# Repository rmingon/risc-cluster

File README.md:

# RISC-V Cluster Project

A distributed computing cluster based on CH32V RISC-V microcontrollers with Ethernet connectivity.

[HACKADAY](https://hackaday.io/project/204036-13ghz-for-only-10-bucks)

[TINDIE](https://www.tindie.com/products/rmingon/risc-v-cluster-13ghz-combined/)

## Overview

This project implements a cluster computing system using multiple CH32V microcontrollers connected via Ethernet. The system features a master controller (CH32V307RCT6) that coordinates with multiple worker nodes (CH32V003F4P6) to form a distributed computing network.

## Project pictures

## Hardware Design

### Master Controller

- **MCU**: CH32V307RCT6 (64-pin LQFP)
- **Features**:
  - RISC-V core with Ethernet MAC
  - USB connectivity for debugging and programming
  - Ethernet port (RJ45) for network communication
  - Power regulation (3.3V via AMS1117)

### Worker Nodes

- **MCU**: CH32V003F4P6 (24 units)
- **Features**:
  - Compact RISC-V microcontrollers
  - Individual LED indicators
  - Test points for debugging
  - Distributed across the PCB

### Key Components

- **Ethernet**: RJ45 connector with integrated magnetics
- **USB**: Micro-B connector for programming and debug
- **Power**: 3.3V regulation from USB input
- **Debug**: CH340C USB-to-UART bridge
- **Connectors**: Programming headers for JTAG/SWD access

## Project Structure

```
risc-cluster/
├── hardware/                 # KiCad PCB design files
│   ├── hardware.kicad_*     # Main PCB design files
│   ├── production/          # Manufacturing files
│   │   ├── bom.csv         # Bill of Materials
│   │   ├── positions.csv   # Pick and place data
│   │   └── hardware.zip    # Gerber files
│   └── hardware-backups/   # Design history backups
└── master/                  # Master controller firmware
    ├── Core/               # RISC-V core files
    ├── Debug/              # Debug utilities
    ├── Peripheral/         # CH32V30x peripheral drivers
    ├── Startup/            # Boot code
    └── User/               # Application code
```

## Bill of Materials

| Component    | Quantity | Description                        |
| ------------ | -------- | ---------------------------------- |
| CH32V307RCT6 | 1        | Master RISC-V MCU (LQFP-64)        |
| CH32V003F4P6 | 24       | Worker RISC-V MCUs (SOP-20)        |
| AMS1117-3.3  | 1        | 3.3V voltage regulator             |
| CH340C       | 1        | USB-to-UART bridge                 |
| LEDs         | 25       | Status indicators                  |
| Resistors    | 29       | Current limiting (0603)            |
| Capacitors   | 52       | Decoupling and filtering (0603)    |
| Connectors   | 5        | USB, Ethernet, programming headers |

## Development Setup

### Hardware Tools

- KiCad 7.0+ for PCB design
- Standard PCB fabrication (4-layer board)
- Pick and place assembly for SMD components

### Software Tools

- MounRiver Studio IDE (for CH32V development)
- WCH-LinkE programmer/debugger
- CH32V peripheral library

## Getting Started

1. **Hardware Assembly**: Use the production files in `hardware/production/` for PCB fabrication
2. **Master Firmware**: Build and flash the master controller code in `master/`
3. **Worker Firmware**: Develop and deploy worker node firmware for distributed tasks
4. **Network Setup**: Configure Ethernet connectivity for cluster communication

## Recent Development

Based on git history, recent work includes:

- Initial PCB layout with CH32V microcontrollers
- Ethernet connectivity implementation
- CH32V307 master controller integration
- MounRiver Studio project setup
- Production file generation

## License

This project is licensed under the CERN Open Hardware Licence Version 2 - Strongly Reciprocal (CERN-OHL-S v2).

The hardware design files are released under CERN-OHL-S v2, which ensures that any modifications or improvements to the hardware design must be shared under the same license terms.

Note: This project uses WCH (Nanjing Qinheng Microelectronics) peripheral libraries for firmware development, which are subject to their own licensing terms.

## Contributing

This is a hardware-software co-design project. Contributions welcome for:

- Firmware optimization
- Hardware design improvements
- Cluster algorithms implementation
- Documentation and examples

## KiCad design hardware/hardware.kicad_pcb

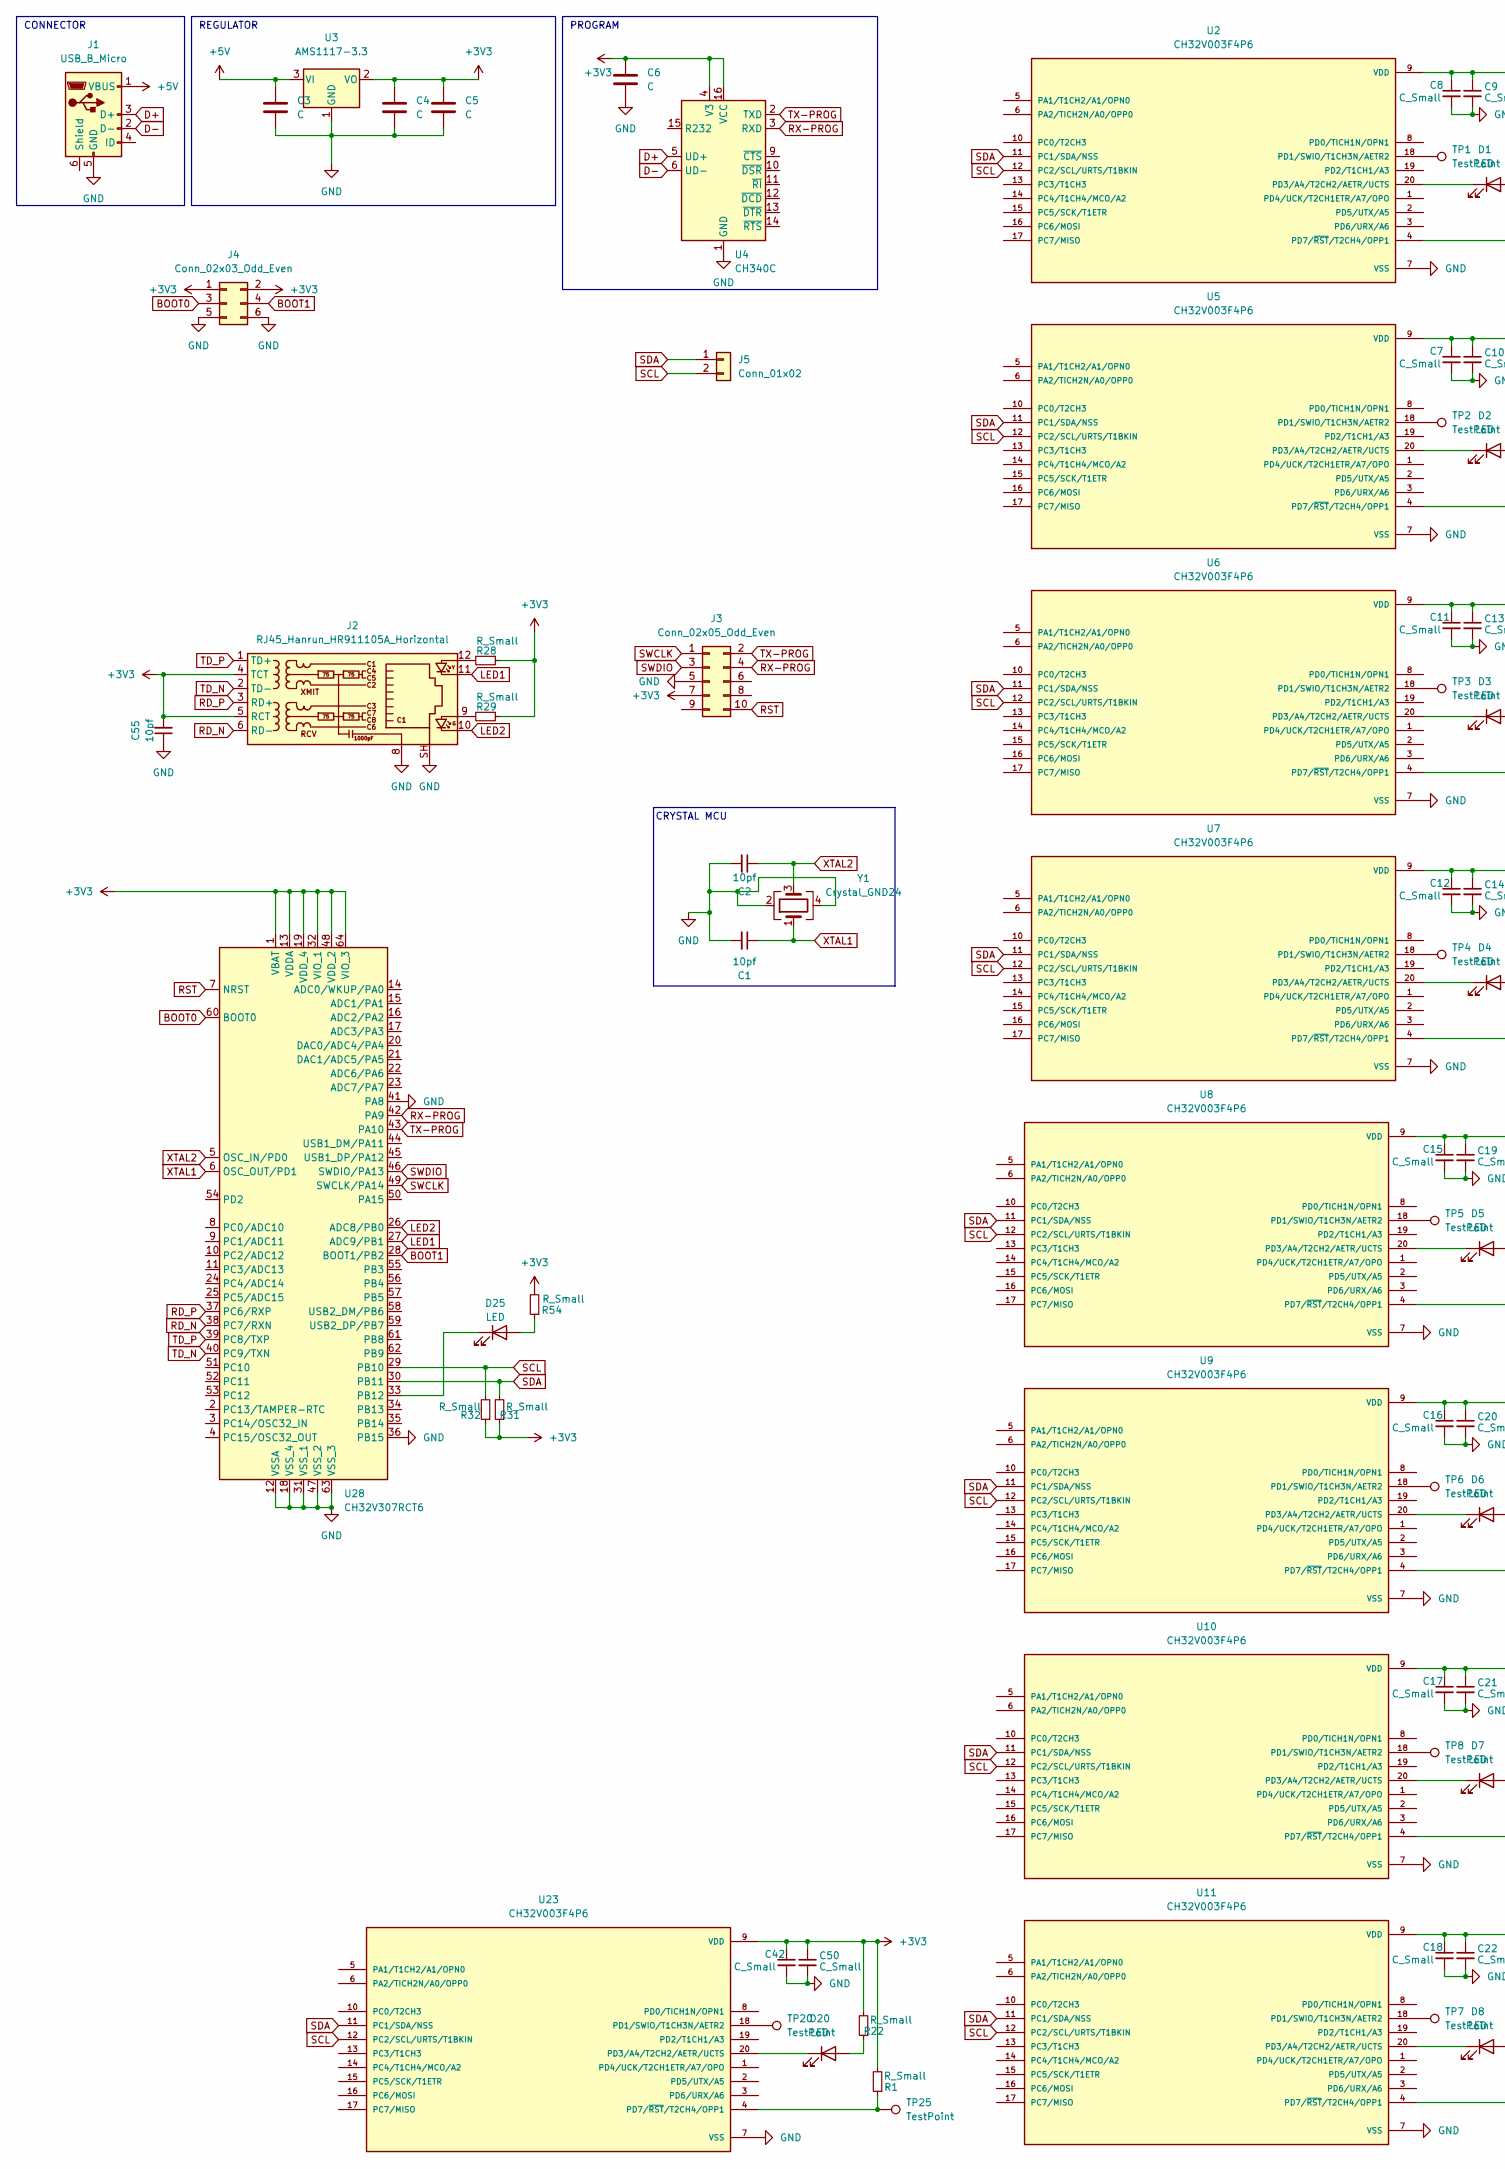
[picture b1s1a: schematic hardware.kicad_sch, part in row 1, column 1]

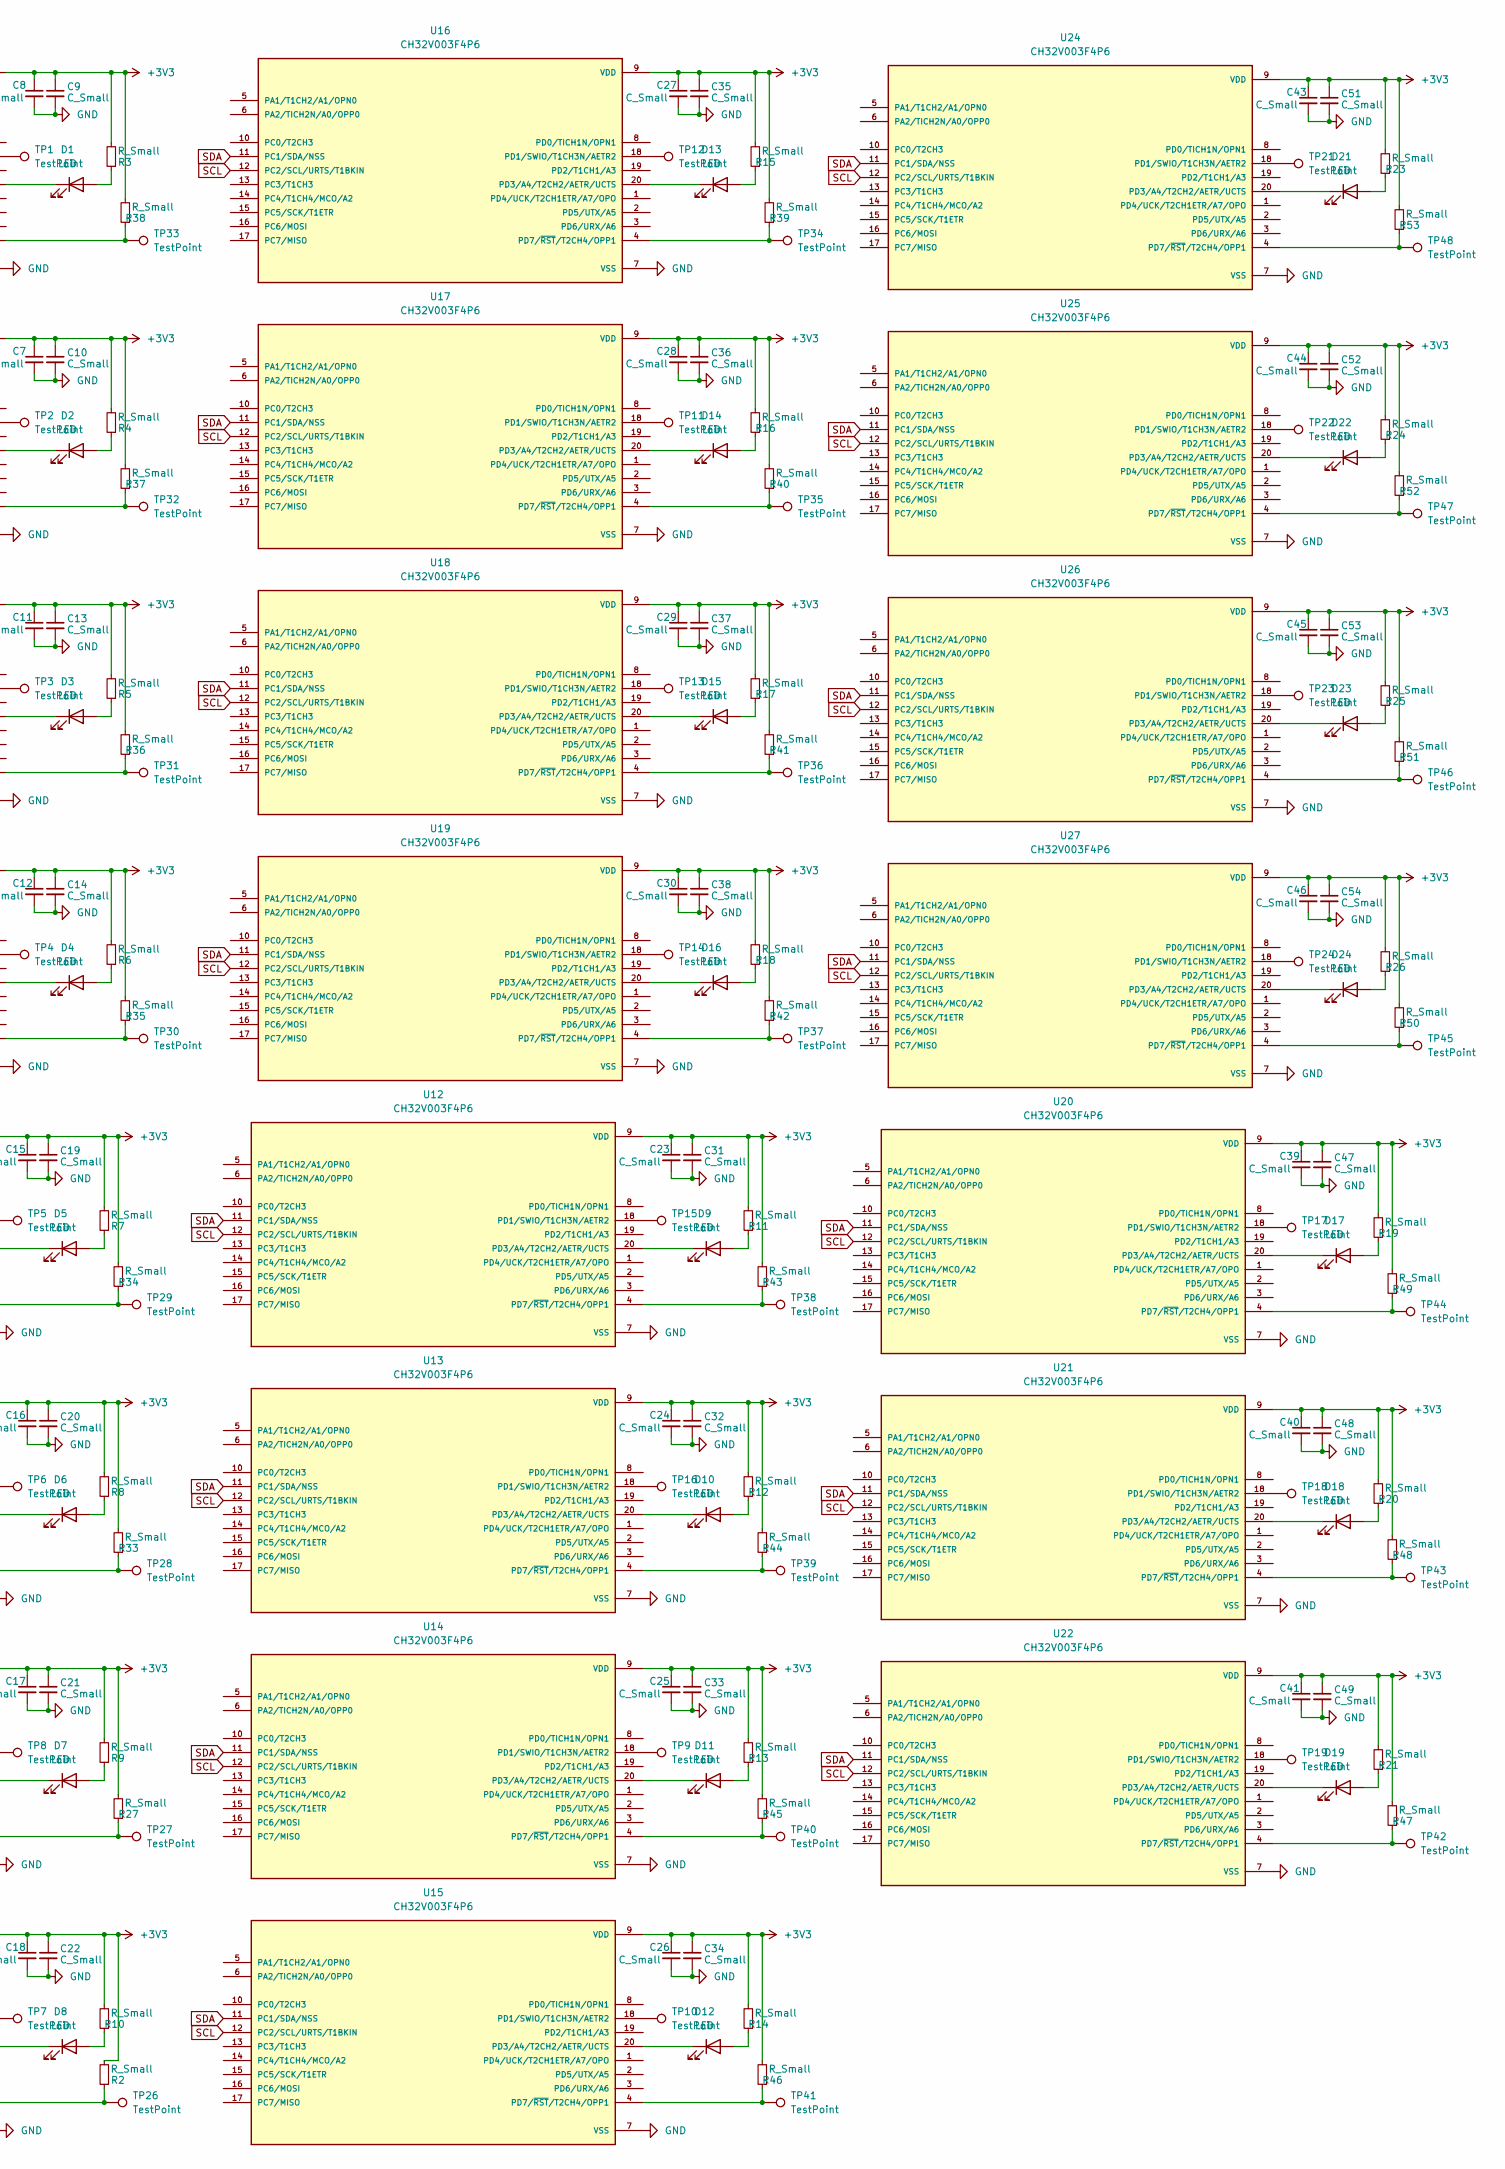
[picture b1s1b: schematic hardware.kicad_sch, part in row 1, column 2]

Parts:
C1, C2, C55: 10pf; C_0603_1608Metric; LCSC C106245
C3, C4, C5, C6: C; C_0603_1608Metric
C7, C8, C9, C10, C11, C12, C13, C14, C15, C16, C17, C18, C19, C20, C21, C22, C23, C24, C25, C26, C27, C28, C29, C30, C31, C32, C33, C34, C35, C36, C37, C38, C39, C40, C41, C42, C43, C44, C45, C46, C47, C48, C49, C50, C51, C52, C53, C54: C_Small; C_0603_1608Metric
D1, D2, D3, D4, D5, D6, D7, D8, D9, D10, D11, D12, D13, D14, D15, D16, D17, D18, D19, D20, D21, D22, D23, D24, D25: LED; LED_0603_1608Metric
J1: USB_B_Micro; USB_Micro-B_Amphenol_10118194_Horizontal
J2: RJ45_Hanrun_HR911105A_Horizontal
J3: Conn_02x05_Odd_Even; PinHeader_2x05_P2.54mm_Vertical
J4: Conn_02x03_Odd_Even; PinHeader_2x03_P2.54mm_Vertical
J5: Conn_01x02; PinHeader_1x02_P2.54mm_Vertical
R1, R2, R3, R4, R5, R6, R7, R8, R9, R10, R11, R12, R13, R14, R15, R16, R17, R18, R19, R20, R21, R22, R23, R24, R25, R26, R27, R28, R29, R31, R32, R33, R34, R35, R36, R37, R38, R39, R40, R41, R42, R43, R44, R45, R46, R47, R48, R49, R50, R51, R52, R53, R54: R_Small; R_0603_1608Metric
TP1, TP2, TP3, TP4, TP5, TP6, TP7, TP8, TP9, TP10, TP11, TP12, TP13, TP14, TP15, TP16, TP17, TP18, TP19, TP20, TP21, TP22, TP23, TP24, TP25, TP26, TP27, TP28, TP29, TP30, TP31, TP32, TP33, TP34, TP35, TP36, TP37, TP38, TP39, TP40, TP41, TP42, TP43, TP44, TP45, TP46, TP47, TP48: TestPoint; TestPoint_Pad_1.0x1.0mm
U2, U5, U6, U7, U8, U9, U10, U11, U12, U13, U14, U15, U16, U17, U18, U19, U20, U21, U22, U23, U24, U25, U26, U27: CH32V003F4P6; SOP65P640X121-20N; PARTREV 1.4
U3: AMS1117-3.3; SOT-223-3_TabPin2
U4: CH340C; SOIC-16_3.9x9.9mm_P1.27mm
U28: CH32V307RCT6; LQFP-64_10x10mm_P0.5mm
Y1: Crystal_GND24; Crystal_SMD_3225-4Pin_3.2x2.5mm_HandSoldering

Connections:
+3V3: C4.1, C5.1, C6.1, C7.1, C8.1, C9.1, C10.1, C11.1, C12.1, C13.1, C14.1, C15.1, C16.1, C17.1, C18.1, C19.1, C20.1, C21.1, C22.1, C23.1, C24.1, C25.1, C26.1, C27.1, C28.1, C29.1, C30.1, C31.1, C32.1, C33.1, C34.1, C35.1, C36.1, C37.1, C38.1, C39.1, C40.1, C41.1, C42.1, C43.1, C44.1, C45.1, C46.1, C47.1, C48.1, C49.1, C50.1, C51.1, C52.1, C53.1, C54.1, C55.2, J2.4 (TCT), J2.5 (RCT), J3.7, J4.1, J4.2, R1.2, R2.2, R3.2, R4.2, R5.2, R6.2, R7.2, R8.2, R9.2, R10.2, R11.2, R12.2, R13.2, R14.2, R15.2, R16.2, R17.2, R18.2, R19.2, R20.2, R21.2, R22.2, R23.2, R24.2, R25.2, R26.2, R27.2, R28.1, R29.1, R31.1, R32.1, R33.2, R34.2, R35.2, R36.2, R37.2, R38.2, R39.2, R40.2, R41.2, R42.2, R43.2, R44.2, R45.2, R46.2, R47.2, R48.2, R49.2, R50.2, R51.2, R52.2, R53.2, R54.2, U2.9 (VDD), U3.2 (VO), U4.4 (V3), U4.16 (VCC), U5.9 (VDD), U6.9 (VDD), U7.9 (VDD), U8.9 (VDD), U9.9 (VDD), U10.9 (VDD), U11.9 (VDD), U12.9 (VDD), U13.9 (VDD), U14.9 (VDD), U15.9 (VDD), U16.9 (VDD), U17.9 (VDD), U18.9 (VDD), U19.9 (VDD), U20.9 (VDD), U21.9 (VDD), U22.9 (VDD), U23.9 (VDD), U24.9 (VDD), U25.9 (VDD), U26.9 (VDD), U27.9 (VDD), U28.1 (VBAT), U28.13 (VDDA), U28.19 (VDD_4), U28.32 (VIO_1), U28.48 (VDD_2), U28.64 (VIO_3)
+5V: C3.1, J1.1 (VBUS), U3.3 (VI)
BOOT0: J4.3, U28.60 (BOOT0)
BOOT1: J4.4, U28.28 (BOOT1/PB2)
D+: J1.3 (D+), U4.5 (UD+)
D-: J1.2 (D-), U4.6 (UD-)
GND: C1.2, C2.2, C3.2, C4.2, C5.2, C6.2, C7.2, C8.2, C9.2, C10.2, C11.2, C12.2, C13.2, C14.2, C15.2, C16.2, C17.2, C18.2, C19.2, C20.2, C21.2, C22.2, C23.2, C24.2, C25.2, C26.2, C27.2, C28.2, C29.2, C30.2, C31.2, C32.2, C33.2, C34.2, C35.2, C36.2, C37.2, C38.2, C39.2, C40.2, C41.2, C42.2, C43.2, C44.2, C45.2, C46.2, C47.2, C48.2, C49.2, C50.2, C51.2, C52.2, C53.2, C54.2, C55.1, J1.5 (GND), J2.8, J2.SH, J3.5, J4.5, J4.6, U2.7 (VSS), U3.1 (GND), U4.1 (GND), U5.7 (VSS), U6.7 (VSS), U7.7 (VSS), U8.7 (VSS), U9.7 (VSS), U10.7 (VSS), U11.7 (VSS), U12.7 (VSS), U13.7 (VSS), U14.7 (VSS), U15.7 (VSS), U16.7 (VSS), U17.7 (VSS), U18.7 (VSS), U19.7 (VSS), U20.7 (VSS), U21.7 (VSS), U22.7 (VSS), U23.7 (VSS), U24.7 (VSS), U25.7 (VSS), U26.7 (VSS), U27.7 (VSS), U28.12 (VSSA), U28.18 (VSS_4), U28.31 (VSS_1), U28.36 (PB15), U28.41 (PA8), U28.47 (VSS_2), U28.63 (VSS_3), Y1.2, Y1.4
LED1: J2.11, U28.27 (ADC9/PB1)
LED2: J2.10, U28.26 (ADC8/PB0)
unnamed: D1.2 (A), R3.1
unnamed: D1.1 (K), U2.20 (PD3/A4/T2CH2/AETR/UCTS)
unnamed: D2.2 (A), R4.1
unnamed: D2.1 (K), U5.20 (PD3/A4/T2CH2/AETR/UCTS)
unnamed: D3.2 (A), R5.1
unnamed: D3.1 (K), U6.20 (PD3/A4/T2CH2/AETR/UCTS)
unnamed: D4.2 (A), R6.1
unnamed: D4.1 (K), U7.20 (PD3/A4/T2CH2/AETR/UCTS)
unnamed: D5.2 (A), R7.1
unnamed: D5.1 (K), U8.20 (PD3/A4/T2CH2/AETR/UCTS)
unnamed: D6.2 (A), R8.1
unnamed: D6.1 (K), U9.20 (PD3/A4/T2CH2/AETR/UCTS)
unnamed: D7.2 (A), R9.1
unnamed: D7.1 (K), U10.20 (PD3/A4/T2CH2/AETR/UCTS)
unnamed: D8.2 (A), R10.1
unnamed: D8.1 (K), U11.20 (PD3/A4/T2CH2/AETR/UCTS)
unnamed: D9.2 (A), R11.1
unnamed: D9.1 (K), U12.20 (PD3/A4/T2CH2/AETR/UCTS)
unnamed: D10.2 (A), R12.1
unnamed: D10.1 (K), U13.20 (PD3/A4/T2CH2/AETR/UCTS)
unnamed: D11.2 (A), R13.1
unnamed: D11.1 (K), U14.20 (PD3/A4/T2CH2/AETR/UCTS)
unnamed: D12.2 (A), R14.1
unnamed: D12.1 (K), U15.20 (PD3/A4/T2CH2/AETR/UCTS)
unnamed: D13.2 (A), R15.1
unnamed: D13.1 (K), U16.20 (PD3/A4/T2CH2/AETR/UCTS)
unnamed: D14.2 (A), R16.1
unnamed: D14.1 (K), U17.20 (PD3/A4/T2CH2/AETR/UCTS)
unnamed: D15.2 (A), R17.1
unnamed: D15.1 (K), U18.20 (PD3/A4/T2CH2/AETR/UCTS)
unnamed: D16.2 (A), R18.1
unnamed: D16.1 (K), U19.20 (PD3/A4/T2CH2/AETR/UCTS)
unnamed: D17.2 (A), R19.1
unnamed: D17.1 (K), U20.20 (PD3/A4/T2CH2/AETR/UCTS)
unnamed: D18.2 (A), R20.1
unnamed: D18.1 (K), U21.20 (PD3/A4/T2CH2/AETR/UCTS)
unnamed: D19.2 (A), R21.1
unnamed: D19.1 (K), U22.20 (PD3/A4/T2CH2/AETR/UCTS)
unnamed: D20.2 (A), R22.1
unnamed: D20.1 (K), U23.20 (PD3/A4/T2CH2/AETR/UCTS)
unnamed: D21.2 (A), R23.1
unnamed: D21.1 (K), U24.20 (PD3/A4/T2CH2/AETR/UCTS)
unnamed: D22.2 (A), R24.1
unnamed: D22.1 (K), U25.20 (PD3/A4/T2CH2/AETR/UCTS)
unnamed: D23.2 (A), R25.1
unnamed: D23.1 (K), U26.20 (PD3/A4/T2CH2/AETR/UCTS)
unnamed: D24.2 (A), R26.1
unnamed: D24.1 (K), U27.20 (PD3/A4/T2CH2/AETR/UCTS)
unnamed: D25.2 (A), R54.1
unnamed: D25.1 (K), U28.33 (PB12)
unnamed: J2.9, R29.2
unnamed: J2.12, R28.2
unnamed: TP1.1, U2.18 (PD1/SWIO/T1CH3N/AETR2)
unnamed: R38.1, TP33.1, U2.4 (PD7/~RST/T2CH4/OPP1)
unnamed: TP2.1, U5.18 (PD1/SWIO/T1CH3N/AETR2)
unnamed: R37.1, TP32.1, U5.4 (PD7/~RST/T2CH4/OPP1)
unnamed: TP3.1, U6.18 (PD1/SWIO/T1CH3N/AETR2)
unnamed: R36.1, TP31.1, U6.4 (PD7/~RST/T2CH4/OPP1)
unnamed: TP4.1, U7.18 (PD1/SWIO/T1CH3N/AETR2)
unnamed: R35.1, TP30.1, U7.4 (PD7/~RST/T2CH4/OPP1)
unnamed: TP5.1, U8.18 (PD1/SWIO/T1CH3N/AETR2)
unnamed: R34.1, TP29.1, U8.4 (PD7/~RST/T2CH4/OPP1)
unnamed: TP6.1, U9.18 (PD1/SWIO/T1CH3N/AETR2)
unnamed: R33.1, TP28.1, U9.4 (PD7/~RST/T2CH4/OPP1)
unnamed: TP8.1, U10.18 (PD1/SWIO/T1CH3N/AETR2)
unnamed: R27.1, TP27.1, U10.4 (PD7/~RST/T2CH4/OPP1)
unnamed: TP7.1, U11.18 (PD1/SWIO/T1CH3N/AETR2)
unnamed: R2.1, TP26.1, U11.4 (PD7/~RST/T2CH4/OPP1)
unnamed: TP15.1, U12.18 (PD1/SWIO/T1CH3N/AETR2)
unnamed: R43.1, TP38.1, U12.4 (PD7/~RST/T2CH4/OPP1)
unnamed: TP16.1, U13.18 (PD1/SWIO/T1CH3N/AETR2)
unnamed: R44.1, TP39.1, U13.4 (PD7/~RST/T2CH4/OPP1)
unnamed: TP9.1, U14.18 (PD1/SWIO/T1CH3N/AETR2)
unnamed: R45.1, TP40.1, U14.4 (PD7/~RST/T2CH4/OPP1)
unnamed: TP10.1, U15.18 (PD1/SWIO/T1CH3N/AETR2)
unnamed: R46.1, TP41.1, U15.4 (PD7/~RST/T2CH4/OPP1)
unnamed: TP12.1, U16.18 (PD1/SWIO/T1CH3N/AETR2)
unnamed: R39.1, TP34.1, U16.4 (PD7/~RST/T2CH4/OPP1)
unnamed: TP11.1, U17.18 (PD1/SWIO/T1CH3N/AETR2)
unnamed: R40.1, TP35.1, U17.4 (PD7/~RST/T2CH4/OPP1)
unnamed: TP13.1, U18.18 (PD1/SWIO/T1CH3N/AETR2)
unnamed: R41.1, TP36.1, U18.4 (PD7/~RST/T2CH4/OPP1)
unnamed: TP14.1, U19.18 (PD1/SWIO/T1CH3N/AETR2)
unnamed: R42.1, TP37.1, U19.4 (PD7/~RST/T2CH4/OPP1)
unnamed: TP17.1, U20.18 (PD1/SWIO/T1CH3N/AETR2)
unnamed: R49.1, TP44.1, U20.4 (PD7/~RST/T2CH4/OPP1)
unnamed: TP18.1, U21.18 (PD1/SWIO/T1CH3N/AETR2)
unnamed: R48.1, TP43.1, U21.4 (PD7/~RST/T2CH4/OPP1)
unnamed: TP19.1, U22.18 (PD1/SWIO/T1CH3N/AETR2)
unnamed: R47.1, TP42.1, U22.4 (PD7/~RST/T2CH4/OPP1)
unnamed: TP20.1, U23.18 (PD1/SWIO/T1CH3N/AETR2)
unnamed: R1.1, TP25.1, U23.4 (PD7/~RST/T2CH4/OPP1)
unnamed: TP21.1, U24.18 (PD1/SWIO/T1CH3N/AETR2)
unnamed: R53.1, TP48.1, U24.4 (PD7/~RST/T2CH4/OPP1)
unnamed: TP22.1, U25.18 (PD1/SWIO/T1CH3N/AETR2)
unnamed: R52.1, TP47.1, U25.4 (PD7/~RST/T2CH4/OPP1)
unnamed: TP23.1, U26.18 (PD1/SWIO/T1CH3N/AETR2)
unnamed: R51.1, TP46.1, U26.4 (PD7/~RST/T2CH4/OPP1)
unnamed: TP24.1, U27.18 (PD1/SWIO/T1CH3N/AETR2)
unnamed: R50.1, TP45.1, U27.4 (PD7/~RST/T2CH4/OPP1)
RD_N: J2.6 (RD-), U28.38 (PC7/RXN)
RD_P: J2.3 (RD+), U28.37 (PC6/RXP)
RST: J3.10, U28.7 (NRST)
RX-PROG: J3.4, U4.3 (RXD), U28.42 (PA9)
SCL: J5.2, R32.2, U2.12 (PC2/SCL/URTS/T1BKIN), U5.12 (PC2/SCL/URTS/T1BKIN), U6.12 (PC2/SCL/URTS/T1BKIN), U7.12 (PC2/SCL/URTS/T1BKIN), U8.12 (PC2/SCL/URTS/T1BKIN), U9.12 (PC2/SCL/URTS/T1BKIN), U10.12 (PC2/SCL/URTS/T1BKIN), U11.12 (PC2/SCL/URTS/T1BKIN), U12.12 (PC2/SCL/URTS/T1BKIN), U13.12 (PC2/SCL/URTS/T1BKIN), U14.12 (PC2/SCL/URTS/T1BKIN), U15.12 (PC2/SCL/URTS/T1BKIN), U16.12 (PC2/SCL/URTS/T1BKIN), U17.12 (PC2/SCL/URTS/T1BKIN), U18.12 (PC2/SCL/URTS/T1BKIN), U19.12 (PC2/SCL/URTS/T1BKIN), U20.12 (PC2/SCL/URTS/T1BKIN), U21.12 (PC2/SCL/URTS/T1BKIN), U22.12 (PC2/SCL/URTS/T1BKIN), U23.12 (PC2/SCL/URTS/T1BKIN), U24.12 (PC2/SCL/URTS/T1BKIN), U25.12 (PC2/SCL/URTS/T1BKIN), U26.12 (PC2/SCL/URTS/T1BKIN), U27.12 (PC2/SCL/URTS/T1BKIN), U28.29 (PB10)
SDA: J5.1, R31.2, U2.11 (PC1/SDA/NSS), U5.11 (PC1/SDA/NSS), U6.11 (PC1/SDA/NSS), U7.11 (PC1/SDA/NSS), U8.11 (PC1/SDA/NSS), U9.11 (PC1/SDA/NSS), U10.11 (PC1/SDA/NSS), U11.11 (PC1/SDA/NSS), U12.11 (PC1/SDA/NSS), U13.11 (PC1/SDA/NSS), U14.11 (PC1/SDA/NSS), U15.11 (PC1/SDA/NSS), U16.11 (PC1/SDA/NSS), U17.11 (PC1/SDA/NSS), U18.11 (PC1/SDA/NSS), U19.11 (PC1/SDA/NSS), U20.11 (PC1/SDA/NSS), U21.11 (PC1/SDA/NSS), U22.11 (PC1/SDA/NSS), U23.11 (PC1/SDA/NSS), U24.11 (PC1/SDA/NSS), U25.11 (PC1/SDA/NSS), U26.11 (PC1/SDA/NSS), U27.11 (PC1/SDA/NSS), U28.30 (PB11)
SWCLK: J3.1, U28.49 (SWCLK/PA14)
SWDIO: J3.3, U28.46 (SWDIO/PA13)
TD_N: J2.2 (TD-), U28.40 (PC9/TXN)
TD_P: J2.1 (TD+), U28.39 (PC8/TXP)
TX-PROG: J3.2, U4.2 (TXD), U28.43 (PA10)
XTAL1: C1.1, U28.6 (OSC_OUT/PD1), Y1.1
XTAL2: C2.1, U28.5 (OSC_IN/PD0), Y1.3

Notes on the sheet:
CONNECTOR
PROGRAM
REGULATOR
CRYSTAL MCU

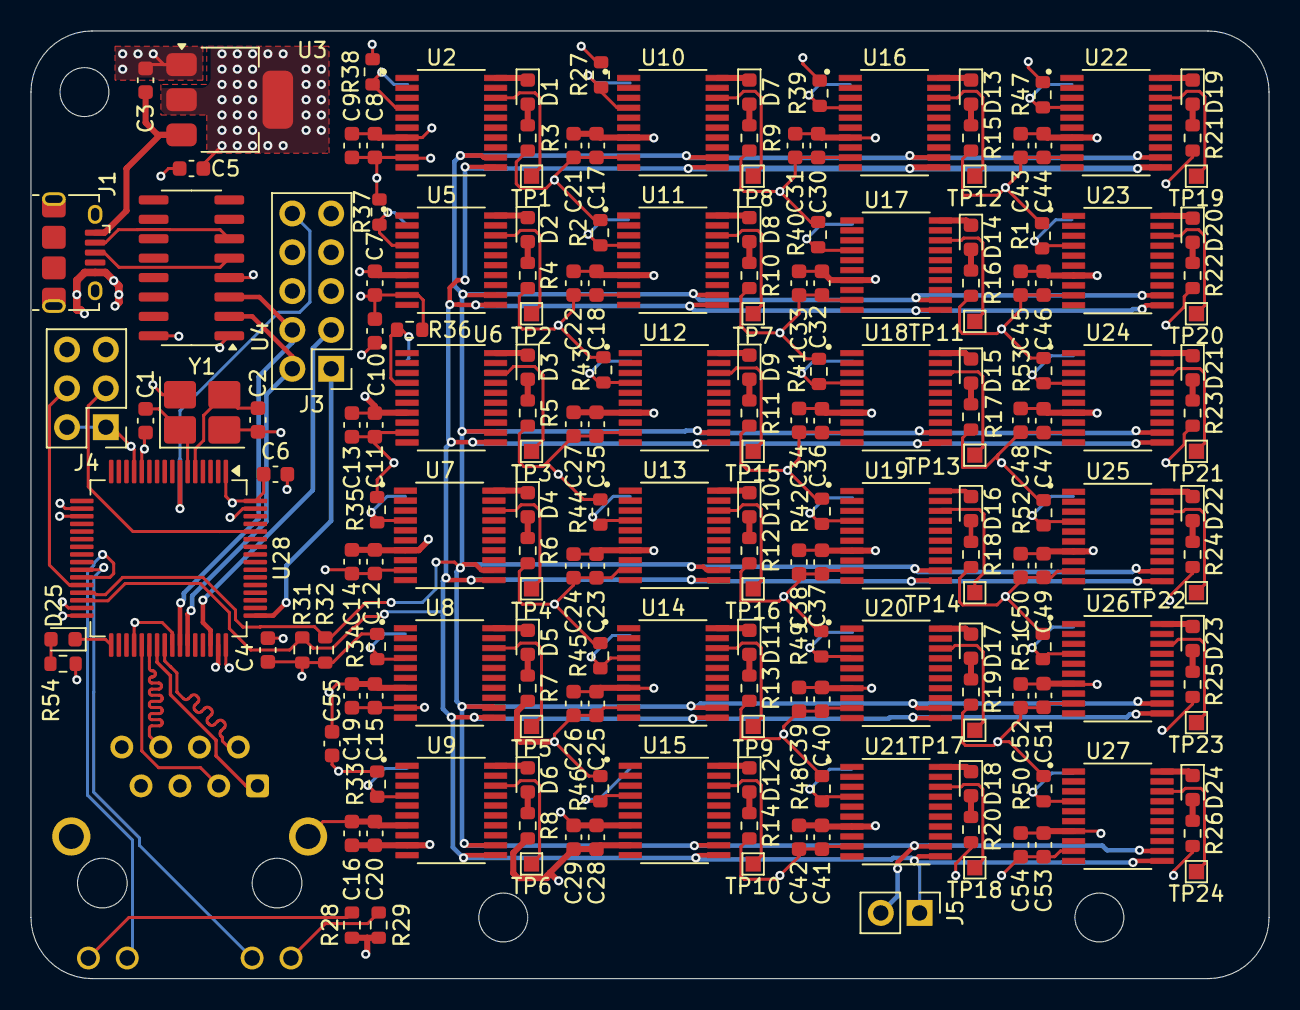
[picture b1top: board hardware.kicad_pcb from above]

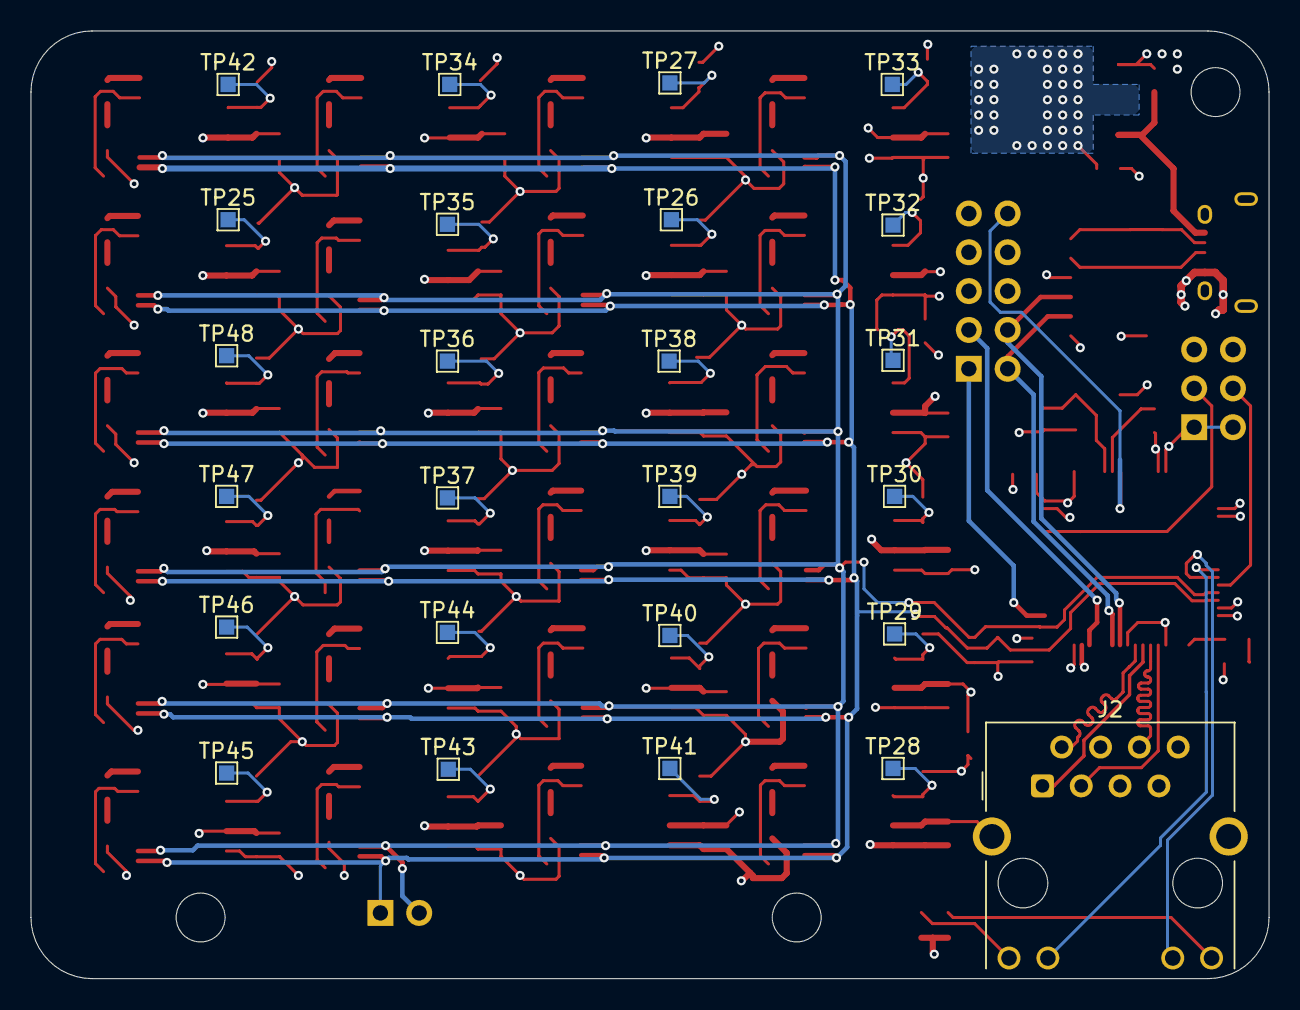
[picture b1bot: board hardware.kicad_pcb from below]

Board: 4 copper layers, 81.0 x 62.0 mm, 214 parts (25 on the bottom side), 122 nets.

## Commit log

2025-07-08 add ch32v003 on pcb
2025-07-09 position capacitor + resistor + led with each ch32
2025-07-11 add wiring ch32v006
2025-07-13 add ethernet wiring
2025-07-15 wiring ch32v307 + ethernet
2025-07-16 add moutriver master project
2025-07-16 add readme
2025-07-16 add slave mounriver project
2025-07-17 add ethernet support
2025-07-29 add external crystal
2025-08-03 update crystal + slave reset pull up
2025-08-04 crystal to gnd
2025-08-21 update ehernet wiring
2025-08-23 pass to 4 layers pcb
2025-08-26 add pictures
2025-08-26 add ethernet
2025-08-26 update with pictures
2025-08-26 update master code for dhcp working
2025-08-26 add dhcp clean project
2025-08-26 add I2C function
2025-08-26 luanch i2c config
2025-08-26 add i2C slave minimal code
2025-08-26 change first slave address
2025-08-26 upgrade 3.3 zone clearance
2025-08-26 upgrade slave code
2025-08-26 add minimal slave bootloader code
2025-09-04 upgrade size
2025-09-04 upgrade master speed
2025-09-04 upgrade buffer number for master PHY socket
2025-09-04 i2c command slave work
2025-09-15 add gif example
2025-09-21 Update README.md
    add tindie and hackaday link
